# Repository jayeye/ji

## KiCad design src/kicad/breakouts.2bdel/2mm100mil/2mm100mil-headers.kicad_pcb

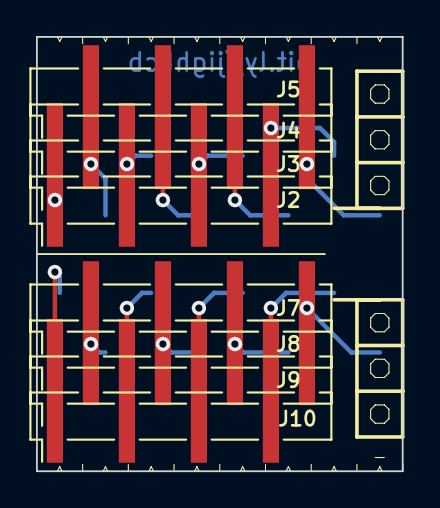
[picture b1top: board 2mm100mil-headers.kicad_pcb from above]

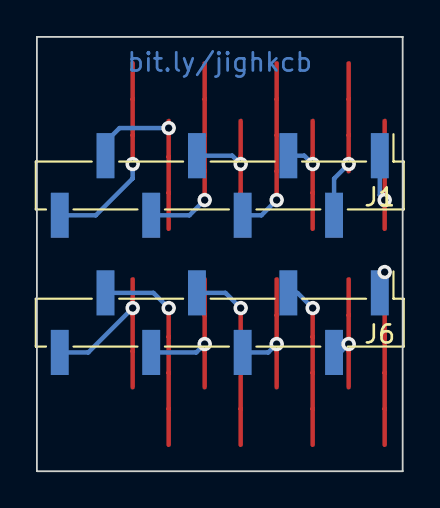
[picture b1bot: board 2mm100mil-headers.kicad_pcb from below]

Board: 2 copper layers, 20.3 x 24.1 mm, 10 parts (2 on the bottom side), 16 nets.

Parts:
J1, J6: Conn_01x08_Male; PinHeader_1x08_P2.54mm_Vertical_SMD_Pin1Left
J2, J3, J4, J5, J7, J8, J9, J10: Conn_01x08_Female; PinSocket_1x08_P2.00mm_Vertical_SMD_Pin1Left

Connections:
/B1: J6.1, J7.1, J8.1, J9.1, J10.1
/B2: J6.2, J7.2, J8.2, J9.2, J10.2
/B3: J6.3, J7.3, J8.3, J9.3, J10.3
/B4: J6.4, J7.4, J8.4, J9.4, J10.4
/B5: J6.5, J7.5, J8.5, J9.5, J10.5
/B6: J6.6, J7.6, J8.6, J9.6, J10.6
/B7: J6.7, J7.7, J8.7, J9.7, J10.7
/B8: J6.8, J7.8, J8.8, J9.8, J10.8
/T1: J1.1, J2.1, J3.1, J4.1, J5.1
/T2: J1.2, J2.2, J3.2, J4.2, J5.2
/T3: J1.3, J2.3, J3.3, J4.3, J5.3
/T4: J1.4, J2.4, J3.4, J4.4, J5.4
/T5: J1.5, J2.5, J3.5, J4.5, J5.5
/T6: J1.6, J2.6, J3.6, J4.6, J5.6
/T7: J1.7, J2.7, J3.7, J4.7, J5.7
/T8: J1.8, J2.8, J3.8, J4.8, J5.8

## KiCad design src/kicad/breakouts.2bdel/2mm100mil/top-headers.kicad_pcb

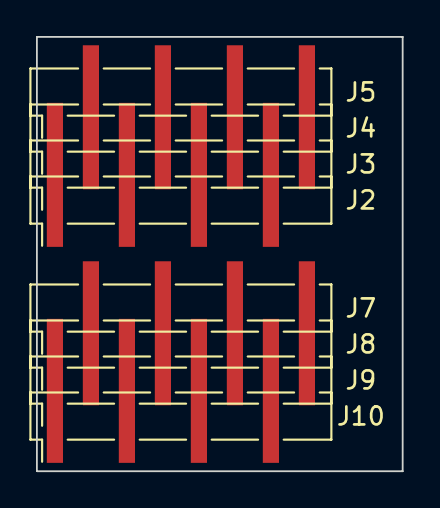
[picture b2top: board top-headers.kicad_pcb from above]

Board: 2 copper layers, 20.3 x 24.1 mm, 8 parts (0 on the bottom side), 16 nets.

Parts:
J2, J3, J4, J5, J7, J8, J9, J10: Conn_01x08_Female; PinSocket_1x08_P2.00mm_Vertical_SMD_Pin1Left

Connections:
/B1: J7.1, J8.1, J9.1, J10.1
/B2: J7.2, J8.2, J9.2, J10.2
/B3: J7.3, J8.3, J9.3, J10.3
/B4: J7.4, J8.4, J9.4, J10.4
/B5: J7.5, J8.5, J9.5, J10.5
/B6: J7.6, J8.6, J9.6, J10.6
/B7: J7.7, J8.7, J9.7, J10.7
/B8: J7.8, J8.8, J9.8, J10.8
/T1: J2.1, J3.1, J4.1, J5.1
/T2: J2.2, J3.2, J4.2, J5.2
/T3: J2.3, J3.3, J4.3, J5.3
/T4: J2.4, J3.4, J4.4, J5.4
/T5: J2.5, J3.5, J4.5, J5.5
/T6: J2.6, J3.6, J4.6, J5.6
/T7: J2.7, J3.7, J4.7, J5.7
/T8: J2.8, J3.8, J4.8, J5.8

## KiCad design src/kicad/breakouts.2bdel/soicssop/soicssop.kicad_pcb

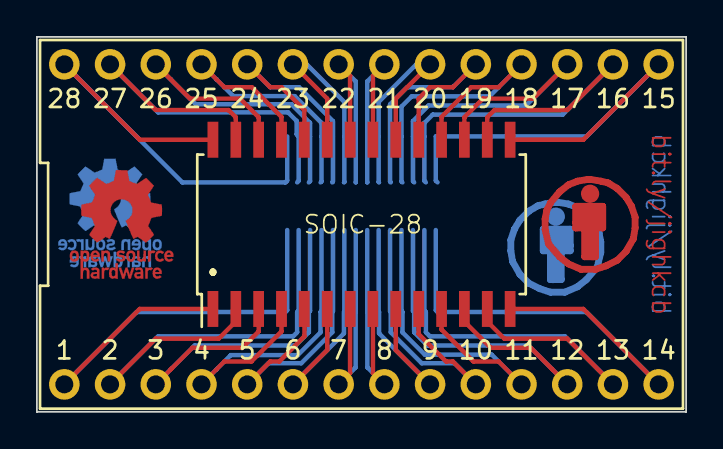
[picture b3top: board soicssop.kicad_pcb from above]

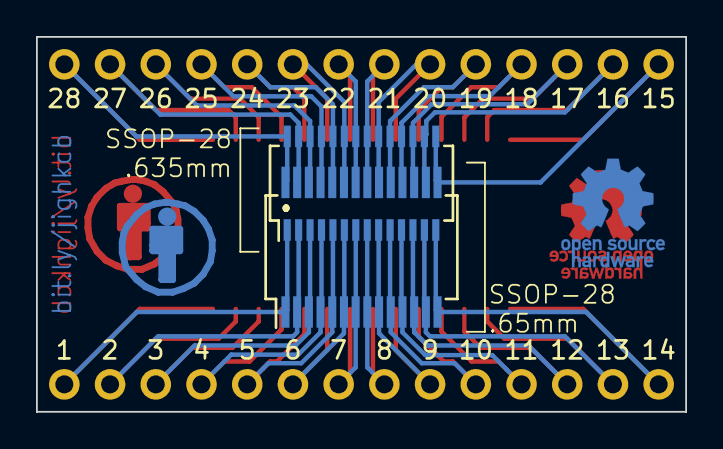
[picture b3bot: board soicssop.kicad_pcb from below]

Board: 2 copper layers, 36.1 x 20.8 mm, 4 parts (2 on the bottom side), 28 nets.

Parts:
J1: DIP-28; DIP-28_700
J2: SOIC-28; SOIC-28W_7.5x17.9mm_P1.27mm
J3: SSOP-28-65; SSOP-28_5.3x10.2mm_P0.65mm
J4: SSOP-28-635; SSOP-28_3.9x9.9mm_P0.635mm

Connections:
/D28_1: J1.1, J2.1, J3.14, J4.14
/D28_2: J1.2, J2.2, J3.13, J4.13
/D28_3: J1.3, J2.3, J3.12, J4.12
/D28_4: J1.4, J2.4, J3.11, J4.11
/D28_5: J1.5, J2.5, J3.10, J4.10
/D28_6: J1.6, J2.6, J3.9, J4.9
/D28_7: J1.7, J2.7, J3.8, J4.8
/D28_8: J1.8, J2.8, J3.7, J4.7
/D28_9: J1.9, J2.9, J3.6, J4.6
/D28_10: J1.10, J2.10, J3.5, J4.5
/D28_11: J1.11, J2.11, J3.4, J4.4
/D28_12: J1.12, J2.12, J3.3, J4.3
/D28_13: J1.13, J2.13, J3.2, J4.2
/D28_14: J1.14, J2.14, J3.1, J4.1
/D28_15: J1.15, J2.15, J3.28, J4.28
/D28_16: J1.16, J2.16, J3.27, J4.27
/D28_17: J1.17, J2.17, J3.26, J4.26
/D28_18: J1.18, J2.18, J3.25, J4.25
/D28_19: J1.19, J2.19, J3.24, J4.24
/D28_20: J1.20, J2.20, J3.23, J4.23
/D28_21: J1.21, J2.21, J3.22, J4.22
/D28_22: J1.22, J2.22, J3.21, J4.21
/D28_23: J1.23, J2.23, J3.20, J4.20
/D28_24: J1.24, J2.24, J3.19, J4.19
/D28_25: J1.25, J2.25, J3.18, J4.18
/D28_26: J1.26, J2.26, J3.17, J4.17
/D28_27: J1.27, J2.27, J3.16, J4.16
/D28_28: J1.28, J2.28, J3.15, J4.15

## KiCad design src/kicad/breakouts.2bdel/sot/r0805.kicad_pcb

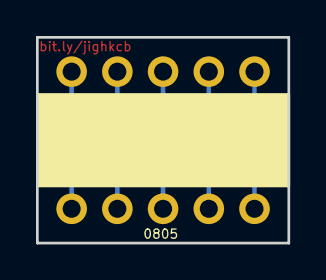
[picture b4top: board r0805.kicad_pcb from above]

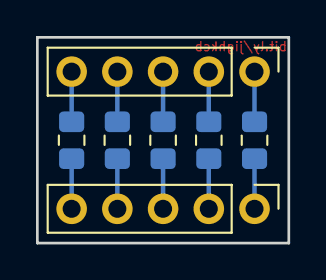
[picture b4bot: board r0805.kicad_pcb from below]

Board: 2 copper layers, 14.0 x 11.4 mm, 7 parts (7 on the bottom side), 10 nets.

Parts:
J10, J13: Conn_01x05_Male; PinHeader_1x05_P2.54mm_Vertical
R6, R7, R8, R9, R10: R; R_0805_2012Metric_Pad1.15x1.40mm_HandSolder

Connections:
unnamed: J10.1, R6.1
unnamed: J10.2, R7.1
unnamed: J10.3, R8.1
unnamed: J10.4, R9.1
unnamed: J10.5, R10.1
unnamed: J13.1, R6.2
unnamed: J13.2, R7.2
unnamed: J13.3, R8.2
unnamed: J13.4, R9.2
unnamed: J13.5, R10.2

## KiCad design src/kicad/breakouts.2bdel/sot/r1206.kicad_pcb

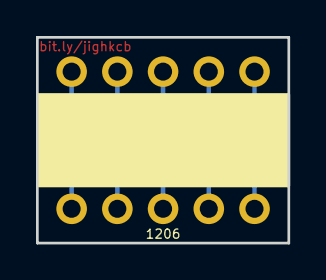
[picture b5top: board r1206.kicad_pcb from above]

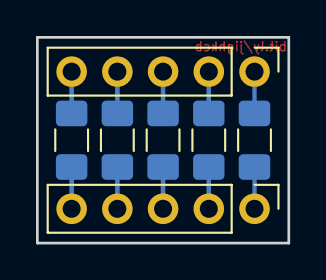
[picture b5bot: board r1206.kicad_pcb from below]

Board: 2 copper layers, 14.0 x 11.4 mm, 7 parts (7 on the bottom side), 10 nets.

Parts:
J6, J8: Conn_01x05_Male; PinHeader_1x05_P2.54mm_Vertical
R1, R2, R3, R4, R5: R; R_1206_3216Metric_Pad1.42x1.75mm_HandSolder

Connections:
unnamed: J6.1, R1.1
unnamed: J6.2, R2.1
unnamed: J6.3, R3.1
unnamed: J6.4, R4.1
unnamed: J6.5, R5.1
unnamed: J8.1, R1.2
unnamed: J8.2, R2.2
unnamed: J8.3, R3.2
unnamed: J8.4, R4.2
unnamed: J8.5, R5.2

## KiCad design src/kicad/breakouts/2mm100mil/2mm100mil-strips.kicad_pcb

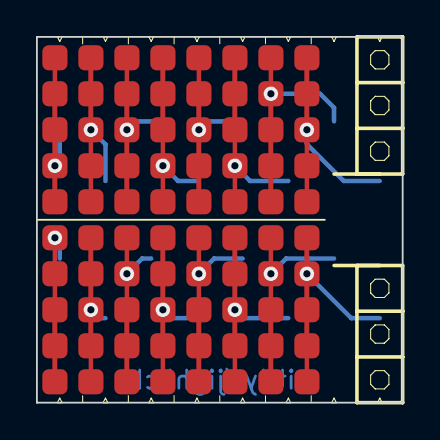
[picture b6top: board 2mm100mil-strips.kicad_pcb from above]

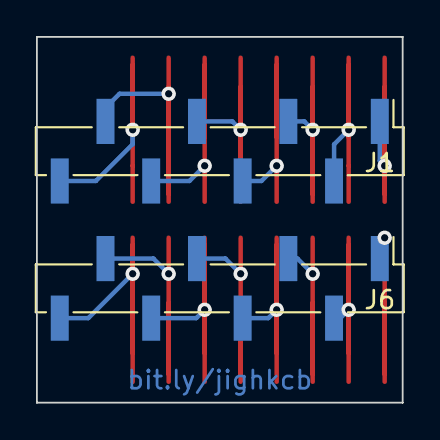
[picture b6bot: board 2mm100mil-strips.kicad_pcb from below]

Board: 2 copper layers, 20.3 x 20.3 mm, 18 parts (2 on the bottom side), 16 nets.

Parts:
J1, J6: Conn_01x08_Male; PinHeader_1x08_P2.54mm_Vertical_SMD_Pin1Left
S1, S2, S3, S4, S5, S6, S7, S8, S9, S10, S11, S12, S13, S14, S15, S16: Conn_01x05; smd1mm4pad-quint

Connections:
/B1: J6.1, S9.1, S9.2, S9.3, S9.4, S9.5
/B2: J6.2, S10.1, S10.2, S10.3, S10.4, S10.5
/B3: J6.3, S11.1, S11.2, S11.3, S11.4, S11.5
/B4: J6.4, S12.1, S12.2, S12.3, S12.4, S12.5
/B5: J6.5, S13.1, S13.2, S13.3, S13.4, S13.5
/B6: J6.6, S14.1, S14.2, S14.3, S14.4, S14.5
/B7: J6.7, S15.1, S15.2, S15.3, S15.4, S15.5
/B8: J6.8, S16.1, S16.2, S16.3, S16.4, S16.5
/T1: J1.1, S1.1, S1.2, S1.3, S1.4, S1.5
/T2: J1.2, S2.1, S2.2, S2.3, S2.4, S2.5
/T3: J1.3, S3.1, S3.2, S3.3, S3.4, S3.5
/T4: J1.4, S4.1, S4.2, S4.3, S4.4, S4.5
/T5: J1.5, S5.1, S5.2, S5.3, S5.4, S5.5
/T6: J1.6, S6.1, S6.2, S6.3, S6.4, S6.5
/T7: J1.7, S7.1, S7.2, S7.3, S7.4, S7.5
/T8: J1.8, S8.1, S8.2, S8.3, S8.4, S8.5
